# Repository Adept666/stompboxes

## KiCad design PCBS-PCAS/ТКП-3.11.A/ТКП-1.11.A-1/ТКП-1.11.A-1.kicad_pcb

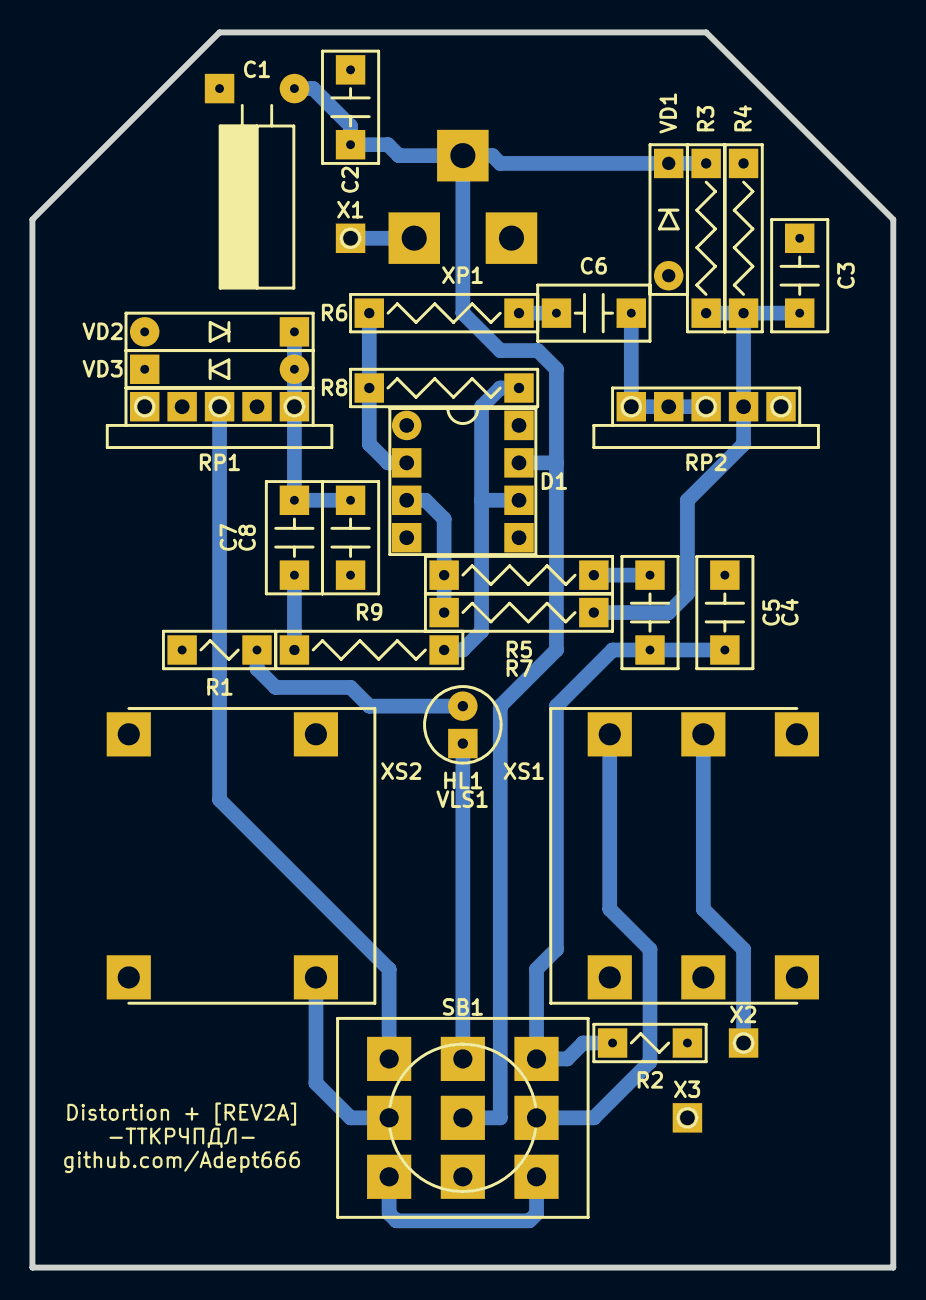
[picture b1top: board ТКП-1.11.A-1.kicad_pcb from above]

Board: 2 copper layers, 58.4 x 83.8 mm, 34 parts (0 on the bottom side), 20 nets.

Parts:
C1: 107; CP-RADIAL-D05.0-P02.0-d0.5-L11-HU
C2: 104; C-DISK-D04.2-T03.0-P05.08-d0.5
C3, C7: 105; C-DISK-D04.2-T03.0-P05.08-d0.5
C4, C8: 102; C-DISK-D04.2-T03.0-P05.08-d0.5
C5: 103; C-DISK-D04.2-T03.0-P05.08-d0.5
C6: 473; C-DISK-D04.2-T03.0-P05.08-d0.5
D1: 741; P-DIP-08
GB1: PP3; B-PP3-HV
HL1: FYL-5013UWC; LED-ROUND-05.0-UNI-SH-SPACER-PNL-5.3
R1: 103; R-MFR-12
R2: 105; R-MFR-12
R3, R4, R7, R8: 105; R-MFR-25
R5, R9: 103; R-MFR-25
R6: 472; R-MFR-25
RP1: A10K; RPB-18-1x17-1.5-PNL-7.4-2.8
RP2: C1M; RPB-18-1x17-1.5-PNL-7.4-2.8
SB1: PBS-24-302SP; SW-PBS-24-302SP-3.0-PNL-13.0
VD1: 400x; P-DO-41
VD2, VD3: 34A; P-DO-7
VE1: B013; B013_A1
VLS1: BR-17.8; VLS-BR
X1: +; CON-PAD-S-1.0-2.0
X2: -; CON-PAD-S-1.0-2.0
X3: COM; CON-PAD-S-1.0-2.0
XP1: 722RA; CON-(L)7X2RA(H)
XS1: NYS215; CON-NYS-215
XS2: NYS2152; CON-NYS-2152

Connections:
/IN-CIR: C4.1, C5.1, R2.2, SB1.NO3
/IN-CON: SB1.COM3, XS1.T
/LED: HL1.A, SB1.NO2
/OUT-CIR: RP1.2, SB1.NO1
/OUT-CON: SB1.COM1, XS2.T
/PP3-NEG: X2.1, XS1.R
/PP3-POS: X1.1, XP1.SN
COM: C1.-, C2.2, C3.2, C4.2, C8.2, D1.4, R1.1, R2.1, R4.1, RP1.1, RP1.NC2, RP2.3, VD1.A, VD2.A, VD3.C, X3.1, XP1.C, XS1.S, XS2.S
unnamed: C5.2, R5.1
unnamed: C6.1, RP2.1, RP2.2, RP2.NC1
unnamed: C6.2, R6.1
unnamed: C7.1, R9.2
unnamed: C7.2, C8.1, RP1.3, VD2.C, VD3.A
unnamed: D1.2, R6.2, R8.1
unnamed: D1.3, R5.2, R7.1
unnamed: D1.6, R8.2, R9.1
unnamed: HL1.C, R1.2
unnamed: SB1.NC1, SB1.NC3
V: C1.+, C2.1, D1.7, R3.2, SB1.COM2, VD1.C, XP1.S
VA: C3.1, R3.1, R4.2, R7.2, RP2.NC2

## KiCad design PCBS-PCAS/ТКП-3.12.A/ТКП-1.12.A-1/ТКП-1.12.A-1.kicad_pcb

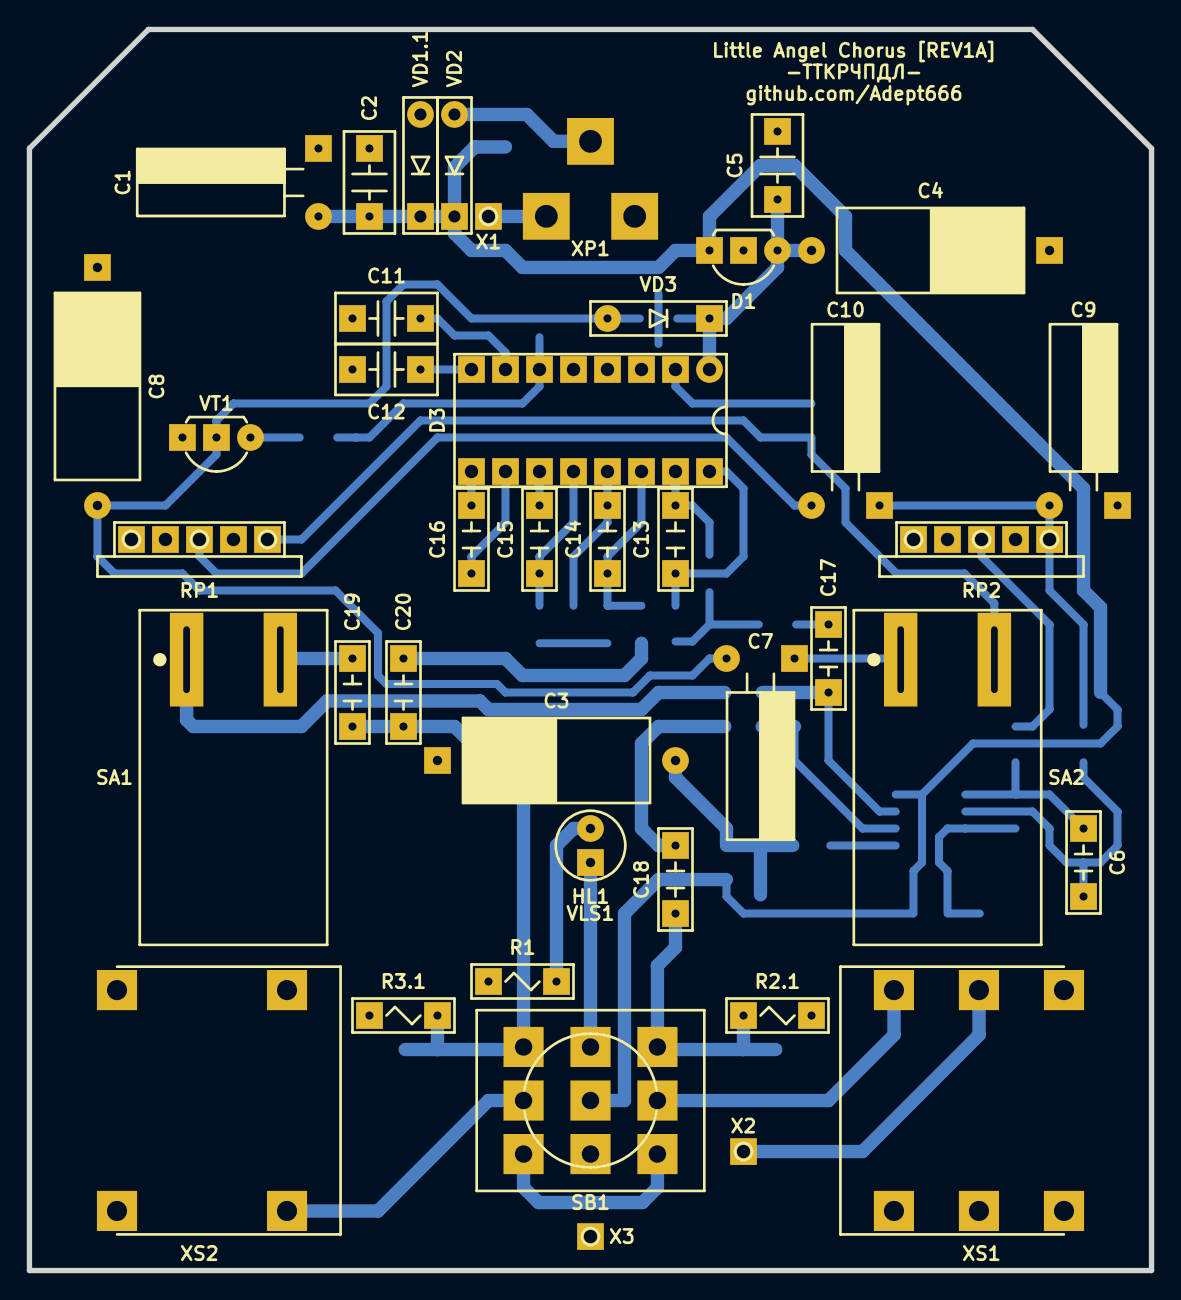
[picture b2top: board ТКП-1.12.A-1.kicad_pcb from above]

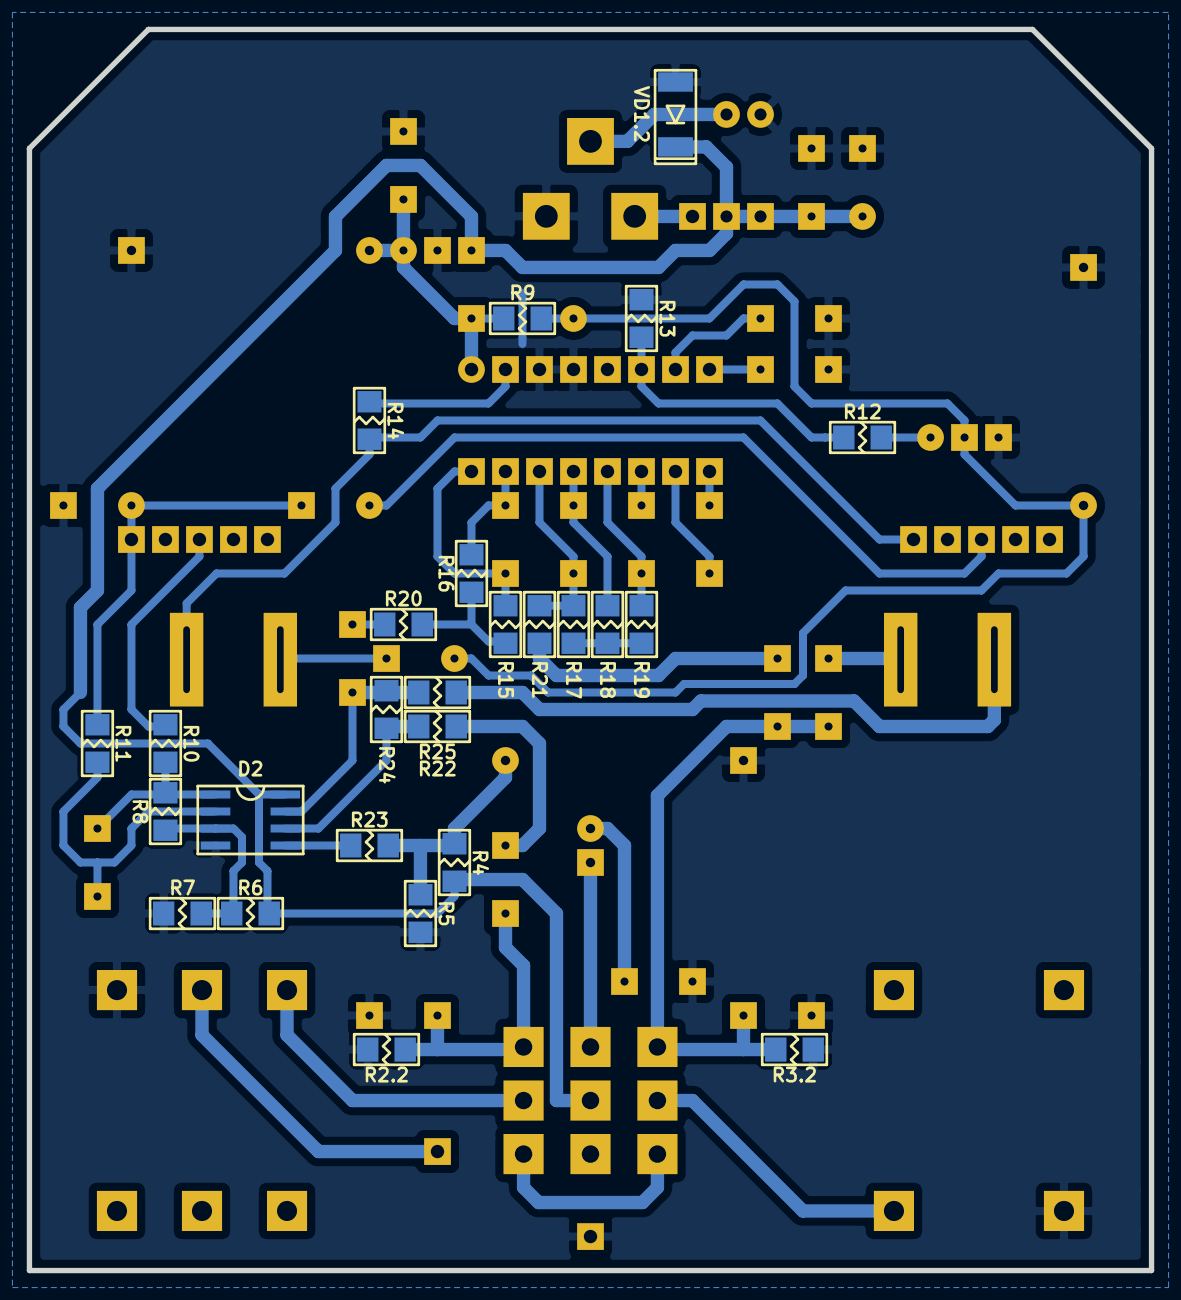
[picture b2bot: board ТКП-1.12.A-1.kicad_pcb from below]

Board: 2 copper layers, 83.8 x 92.7 mm, 70 parts (26 on the bottom side), 46 nets.

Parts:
C1: 107; CP-RADIAL-D05.0-P02.0-d0.5-L11-HU
C2, C5, C11, C12: 104; C-DISK-D04.2-T03.0-P05.08-d0.5
C3, C4, C8: 476; CP-AXIAL-D06-L13-d0.6
C6, C15, C16: 103; C-RECT-L07.3-W02.5-P05.08-d0.5
C7: 106; CP-RADIAL-D05.0-P02.0-d0.5-L11-HD
C9, C10: 106; CP-RADIAL-D05.0-P02.0-d0.5-L11-HU
C13: 332; C-RECT-L07.3-W02.5-P05.08-d0.5
C14: 102; C-RECT-L07.3-W02.5-P05.08-d0.5
C17, C18, C19, C20: 104; C-RECT-L07.3-W02.5-P05.08-d0.5
D1: 78L05; P-TO-92-OUT-GND-IN
D2: 5532; P-SO-08
D3: 2399; P-DIP-16
GB1: PP3; B-PP3-HV
HL1: FYL-5013UWC; LED-ROUND-05.0-UNI-SH-SPACER-PNL-5.3
R1: 103; R-MFR-12
R2.1: 105; R-MFR-12
R2.2, R24: 105; R-SM-1206
R3.1: 104; R-MFR-12
R3.2, R6: 104; R-SM-1206
R4, R5, R15, R16, R17, R18, R19, R20, R21, R25: 103; R-SM-1206
R7: 473; R-SM-1206
R8, R11: 224; R-SM-1206
R9: 683; R-SM-1206
R10: 472; R-SM-1206
R12: 101; R-SM-1206
R13: 222; R-SM-1206
R14: 333; R-SM-1206
R22: 474; R-SM-1206
R23: 334; R-SM-1206
RP1, RP2: B50K; RPB-18-1x12-1.5-PNL-7.4-2.2
SA1, SA2: KN3-1; SW-KN3-1-PNL-13.0
SB1: PBS-24-302SP; SW-PBS-24-302SP-3.0-PNL-13.0
VD1.1: X; P-DO-41
VD1.2: X; P-SOD-87
VD2: 5817; P-DO-41
VD3: 4148; P-DO-35
VE1: G0473; G0473_A1
VLS1: BR-17.8; VLS-BR
VT1: 3904; P-TO-92-C-B-E
X1: +; CON-PAD-S-1.0-2.0
X2: -; CON-PAD-S-1.0-2.0
X3: COM; CON-PAD-S-1.0-2.0
XP1: 722RA; CON-(L)7X2RA(H)
XS1: NYS215; CON-NYS-215
XS2: NYS2152; CON-NYS-2152

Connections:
/IN-CIR: C18.1, R2.1.2, R2.2.2, SB1.NO3
/IN-CON: SB1.COM3, XS1.T
/LED: HL1.A, SB1.NO2
/OUT-CIR: C19.2, C20.2, R3.1.2, R3.2.2, SB1.NO1
/OUT-CON: SB1.COM1, XS2.T
/PP3-NEG: X2.1, XS1.R
/PP3-POS: X1.1, XP1.SN
COM: C1.-, C2.2, C3.-, C4.-, C5.2, C8.-, C9.-, C11.1, C12.1, D1.GND, D2.4, D3.3, D3.4, R1.1, R2.1.1, R2.2.1, R3.1.1, R3.2.1, R5.1, R7.1, R13.1, VD1.1.A, VD1.2.A, VT1.E, X3.1, XP1.C, XS1.S, XS2.S
unnamed: C6.1, D2.1, R8.2, R10.1
unnamed: C6.2, D2.2, R11.1
unnamed: C7.+, C8.+, R9.1, VD3.A, VT1.B
unnamed: C7.-, SA2.COM
unnamed: C10.+, RP1.2
unnamed: C9.+, C10.-, R11.2, RP2.3
unnamed: C11.2, D3.7
unnamed: C12.2, D3.8
unnamed: C13.1, D3.16, R15.1
unnamed: C13.2, D3.15, R16.1
unnamed: C14.1, D3.14, R17.1, R21.1
unnamed: C14.2, D3.13, R18.1
unnamed: C15.1, D3.12, R19.1
unnamed: C15.2, D3.11
unnamed: C16.1, D3.10
unnamed: C16.2, D3.9
unnamed: C17.1, R20.2
unnamed: C17.2, D2.7, R24.2, R25.1
unnamed: C18.2, R22.1
unnamed: C19.1, SA1.NO
unnamed: C20.1, R21.2
unnamed: D2.5, R23.2
unnamed: D2.6, R22.2, R24.1
unnamed: D3.2, R14.2
unnamed: D3.6, R12.2, R13.2
unnamed: HL1.C, R1.2
unnamed: R10.2, RP2.2
unnamed: R12.1, VT1.C
unnamed: R14.1, RP1.3, SA2.NO
unnamed: R15.2, R16.2, R20.1
unnamed: R17.2, R18.2, R19.2
unnamed: R25.2, SA1.COM
unnamed: SB1.NC1, SB1.NC3
unnamed: VD2.A, XP1.S
V: C1.+, C2.1, D1.IN, D2.8, R4.2, R6.2, SB1.COM2, VD1.1.C, VD1.2.C, VD2.C
VA: C4.+, C5.1, D1.OUT, D3.1, R9.2, VD3.C
VB: C3.+, R4.1, R5.2, R23.1
VC: D2.3, R6.1, R7.2, R8.1

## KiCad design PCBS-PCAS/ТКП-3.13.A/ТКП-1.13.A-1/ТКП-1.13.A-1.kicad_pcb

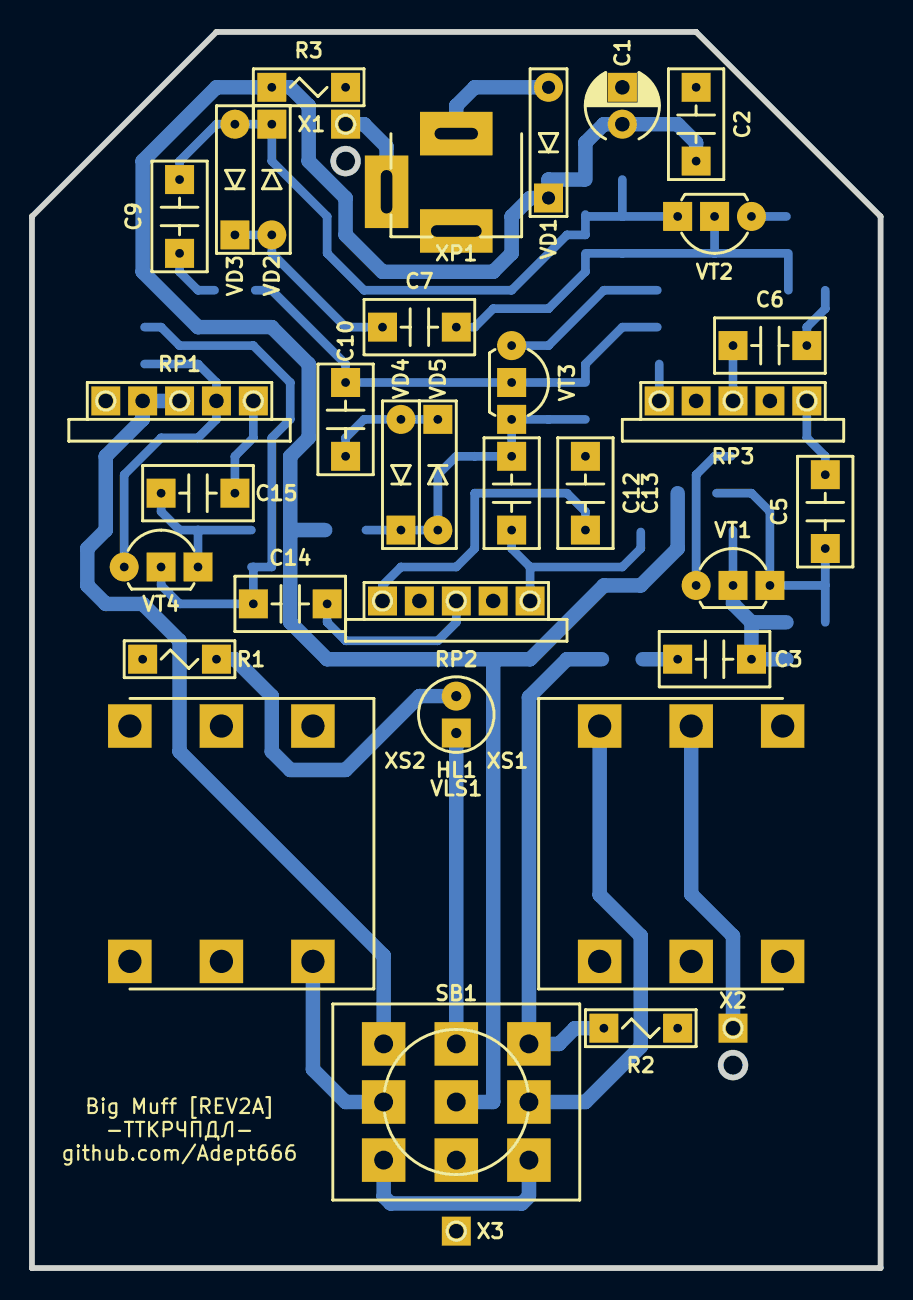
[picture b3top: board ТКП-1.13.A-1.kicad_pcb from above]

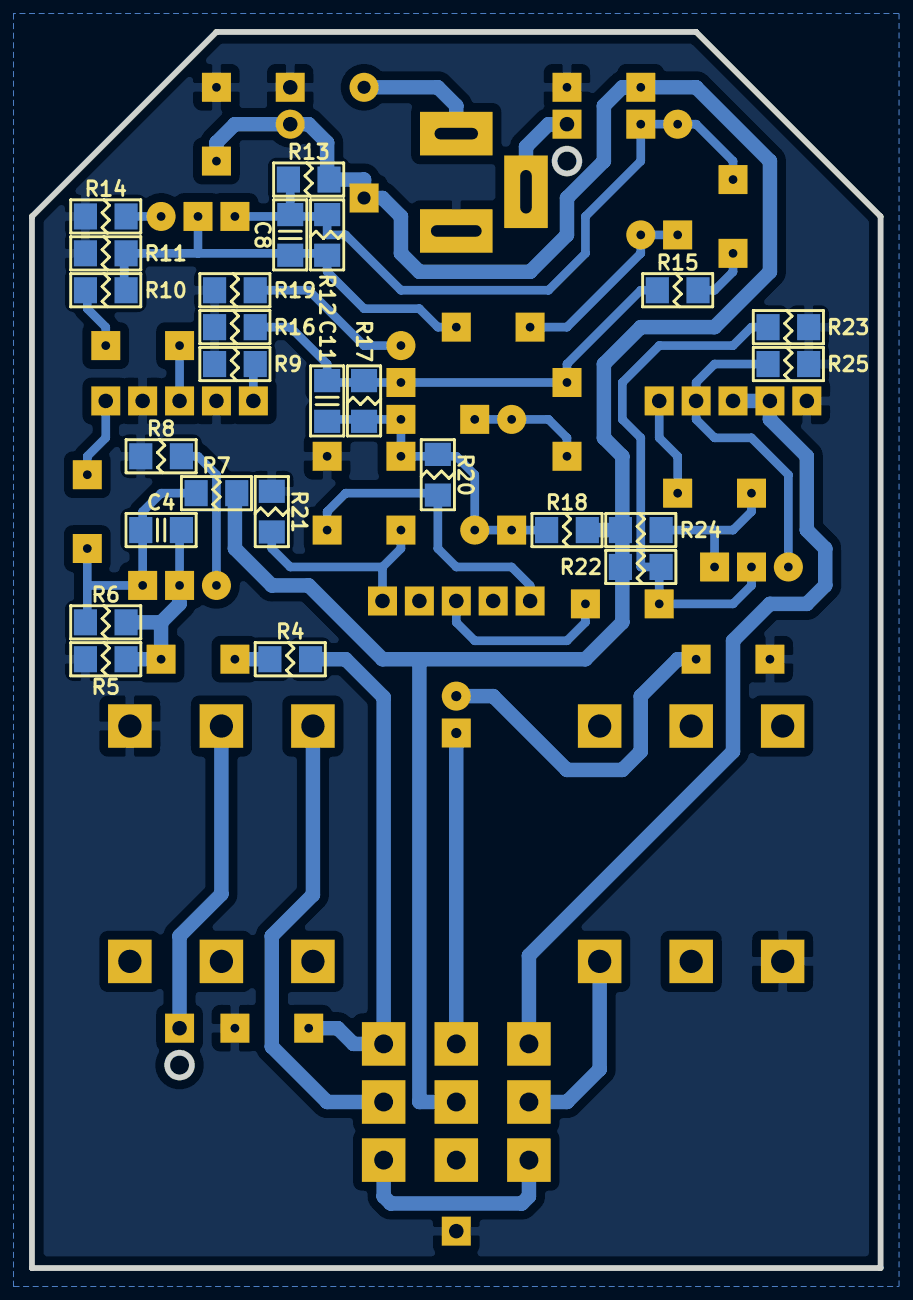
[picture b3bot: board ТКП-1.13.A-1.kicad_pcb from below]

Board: 2 copper layers, 58.4 x 85.1 mm, 63 parts (25 on the bottom side), 36 nets.

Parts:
C1: 106; CP-RADIAL-D05.0-P02.0-CLS
C2: 104; C-DISK-D04.2-T03.0-P05.08-d0.5
C3, C5, C6, C7, C9, C10, C14, C15: 105; C-DISK-D04.2-T03.0-P05.08-d0.5
C4, C8, C11: 471; C-SM-1206
C12: 392; C-DISK-D04.2-T03.0-P05.08-d0.5
C13: 103; C-DISK-D04.2-T03.0-P05.08-d0.5
GB1: PP3; B-PP3-HV
HL1: FYL-5013UWC; LED-ROUND-05.0-UNI-SH-SPACER-PNL-5.3
R1: 103; R-MFR-12
R2: 105; R-MFR-12
R3: X; R-MFR-12
R4: 393; R-SM-1206
R5, R11, R16, R23: 104; R-SM-1206
R6: 514; R-SM-1206
R7, R10, R13, R15, R18, R24: 103; R-SM-1206
R8: 101; R-SM-1206
R9: 182; R-SM-1206
R12, R17, R22: 474; R-SM-1206
R14, R19: 391; R-SM-1206
R20, R21: 223; R-SM-1206
R25: 202; R-SM-1206
RP1, RP3: A100K; RPB-18-1x17-1.5-PNL-7.4-2.8
RP2: B100K; RPB-18-1x17-1.5-PNL-7.4-2.8
SB1: PBS-24-302SP; SW-PBS-24-302SP-3.0-PNL-13.0
VD1: 5817; P-DO-41
VD2, VD3, VD4, VD5: 6263; P-DO-35
VE1: B013; B013_B1
VLS1: BR-17.8; VLS-BR
VT1, VT2, VT3, VT4: 5088; P-TO-92-E-B-C
X1: +; CON-PAD-S-1.0-2.0
X2: -; CON-PAD-S-1.0-2.0
X3: COM; CON-PAD-S-1.0-2.0
XP1: DC-005S; CON-DC-005S
XS1, XS2: PJ-644C; CON-PJ-644C

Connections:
/IN-CIR: R2.2, R4.1, SB1.NO3
/IN-CON: SB1.COM3, XS1.T
/LED: HL1.A, SB1.NO2
/OUT-CIR: RP1.2, RP1.NC1, SB1.NO1
/OUT-CON: SB1.COM1, XS2.T
/PP3-NEG: X2.1, XS1.R
/PP3-POS: X1.1, XP1.SN
COM: C1.-, C2.2, C13.2, R1.1, R2.1, R3.1, R5.1, R8.1, R9.1, R11.1, R14.1, R16.1, R19.1, R21.2, R23.1, R25.1, RP1.1, RP3.NC1, RP3.NC2, X3.1, XP1.C, XS1.S, XS2.S
unnamed: C3.1, R4.2
unnamed: C3.2, C4.1, R5.2, R6.1, VT1.B
unnamed: C4.2, C5.1, R6.2, R7.1, VT1.C
unnamed: C5.2, RP3.3
unnamed: C6.1, RP3.2
unnamed: C6.2, R10.1
unnamed: C7.1, C8.1, R10.2, R11.2, R12.1, VT2.B
unnamed: C7.2, VD2.A, VD3.C
unnamed: C8.2, C9.1, R12.2, R13.1, VD2.C, VD3.A, VT2.C
unnamed: C9.2, R15.1
unnamed: C10.1, C11.1, R15.2, R16.2, R17.1, VT3.B
unnamed: C10.2, VD4.A, VD5.C
unnamed: C11.2, C12.1, R17.2, R18.1, R20.1, VD4.C, VD5.A, VT3.C
unnamed: C12.2, R21.1, RP2.3
unnamed: C13.1, R20.2, RP2.1
unnamed: C14.1, RP2.2
unnamed: C14.2, R22.1, R23.2, VT4.B
unnamed: C15.1, R24.1, VT4.C
unnamed: C15.2, RP1.3
unnamed: HL1.C, R1.2
unnamed: R8.2, VT1.E
unnamed: R9.2, RP3.1
unnamed: R14.2, VT2.E
unnamed: R19.2, VT3.E
unnamed: R25.2, VT4.E
unnamed: SB1.NC1, SB1.NC3
unnamed: VD1.A, XP1.S
V: C1.+, C2.1, R3.2, R7.2, R13.2, R18.2, R22.2, R24.2, SB1.COM2, VD1.C

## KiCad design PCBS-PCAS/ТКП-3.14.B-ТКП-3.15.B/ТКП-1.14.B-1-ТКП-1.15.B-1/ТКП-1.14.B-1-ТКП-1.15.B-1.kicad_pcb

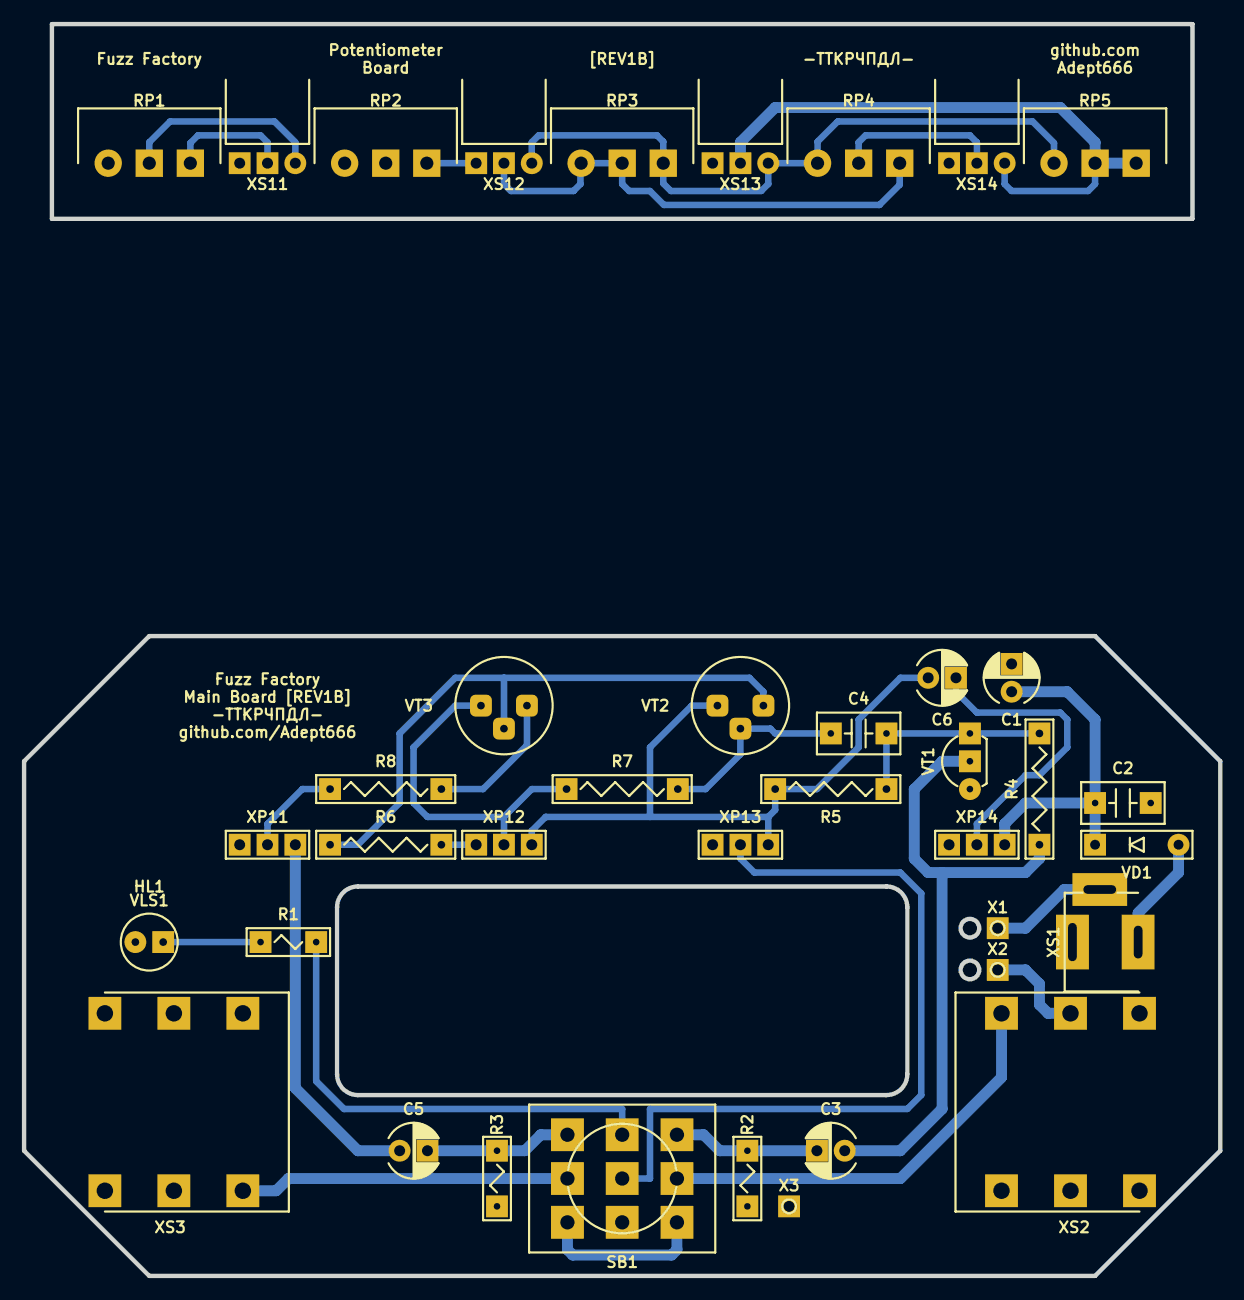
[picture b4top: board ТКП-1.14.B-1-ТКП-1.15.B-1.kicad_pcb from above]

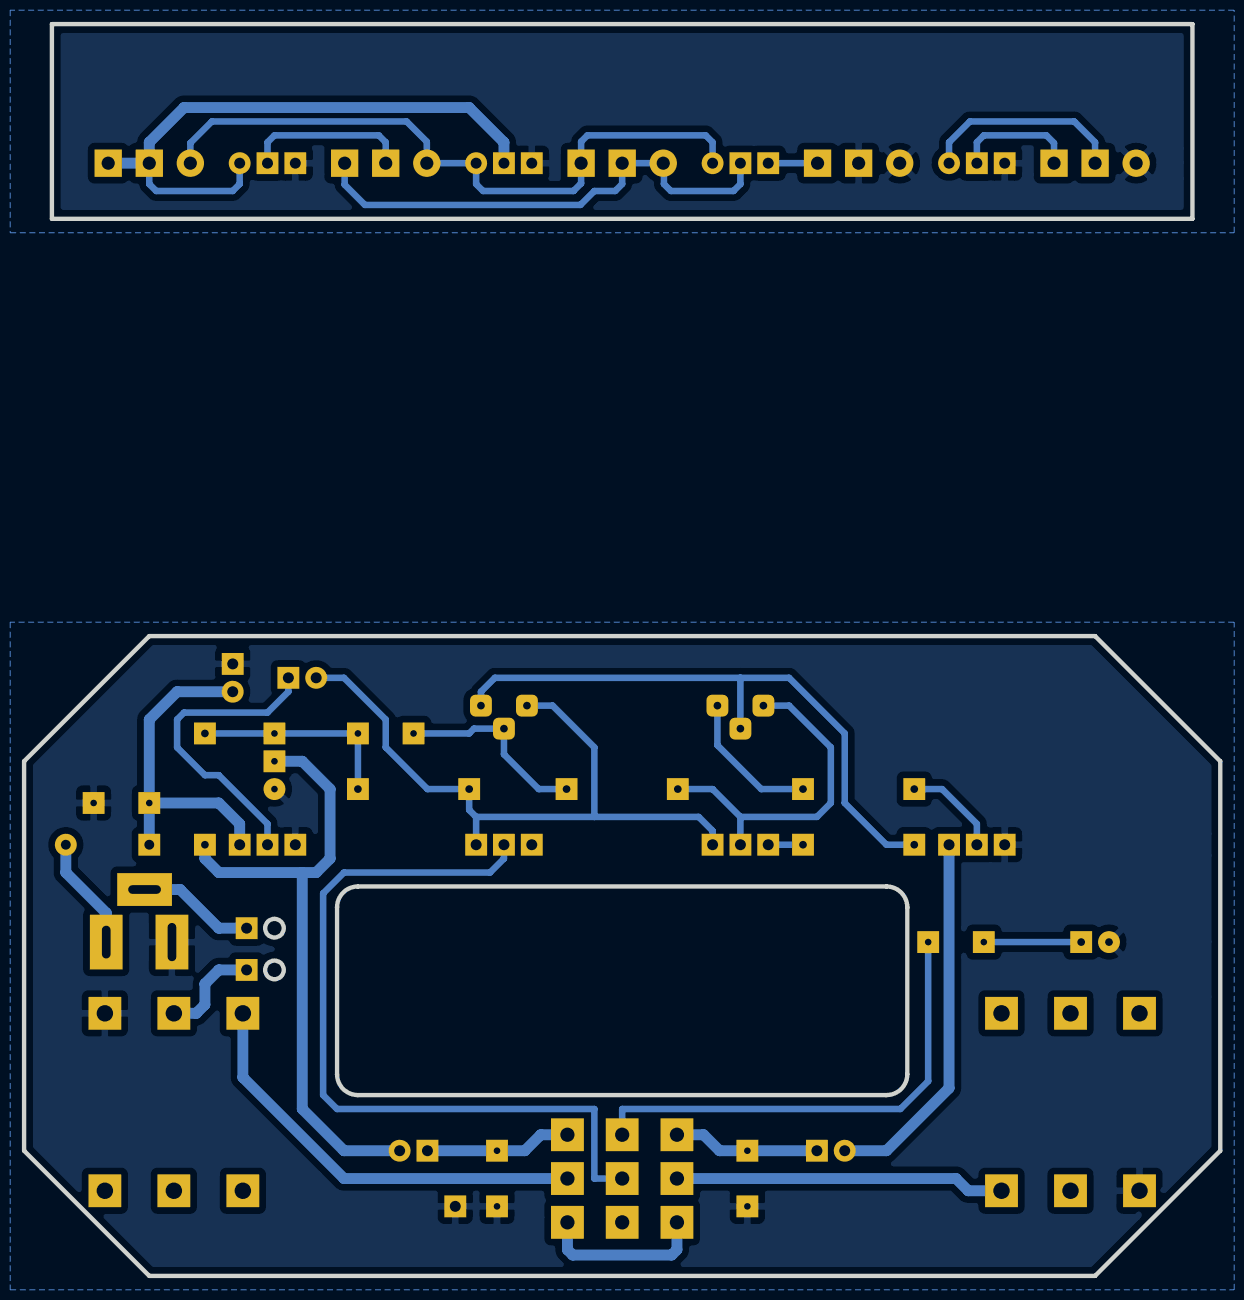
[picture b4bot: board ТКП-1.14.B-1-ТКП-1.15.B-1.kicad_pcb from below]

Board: 2 copper layers, 109.2 x 58.4 mm, 48 parts (6 on the bottom side), 31 nets.

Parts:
C1: 107; CP-RADIAL-D05.0-P02.0-CLS
C2, C4: 104; C-DISK-D04.2-T03.0-P05.08-d0.5
C3, C5, C6: 106; CP-RADIAL-D05.0-P02.0-CLS
GB1: PP3; B-PP3-HV
HL1: FYL-5013UWC; LED-ROUND-05.0-UNI-SH-SPACER-PNL-5.3
R1: 103; R-MFR-12
R2: 105; R-MFR-12
R3: 224; R-MFR-12
R4: 224; R-MFR-25
R5: 103; R-MFR-25
R6: 471; R-MFR-25
R7: 473; R-MFR-25
R8: 512; R-MFR-25
RP1, RP5: B5K; RP-RK1233N1-L15-KC
RP2, RP3, RP4: B10K; RP-RK1233N1-L15-KC
SB1: PBS-24-302SP; SW-PBS-24-302SP-3.0-PNL-13.0
VD1: 5817; P-DO-41
VE1: B013; B013_C1
VJ1.1, VJ1.2, VJ2.1, VJ2.2: BOTTOM; VJ
VLS1: BR-17.8; VLS-BR
VT1: 3904; P-TO-92-E-B-C
VT2, VT3: МП40; P-КТЮ-3-6
VTC1, VTC2: BOTTOM; VTC
X1: +; CON-PAD-S-1.0-2.0
X2: -; CON-PAD-S-1.0-2.0
X3: COM; CON-PAD-S-1.0-2.0
XP11, XP12, XP13, XP14: PLS-03; CON-PLS-03
XS1: DC-005; CON-DC-005
XS2, XS3: PJ-644C; CON-PJ-644C
XS11, XS12, XS13, XS14: PBS-03R; CON-PBS-03R

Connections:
/IN-CIR: C3.-, R2.2, SB1.NO3
/IN-CON: SB1.COM3, XS2.T
/LED: R1.2, SB1.NO2, VJ2.2.1
/MB1: R8.1, XP11.2
/MB2: C5.+, XP11.1
/MB3: R6.1, XP12.3
/MB4: R7.2, VT3.E, XP12.2
/MB5: C6.+, R5.2, VT2.E, XP12.1, XP13.1
/MB7: C6.-, XP14.2
/OUT-CIR: C5.-, R3.2, SB1.NO1
/OUT-CON: SB1.COM1, XS3.T
/PB1: RP1.3, XS11.2
/PB2: RP1.2, XS11.1
/PB3: RP2.3, XS12.3
/PB4: RP3.1, RP3.2, RP4.3, XS12.2
/PB5: RP3.3, RP4.1, RP5.1, XS12.1, XS13.1
/PB7: RP4.2, XS14.2
/PBCOM: RP1.1, RP2.1, RP2.2, XS11.3, XS13.3, XS14.3
/PBV: RP5.2, RP5.3, XS13.2, XS14.1
/PP3-NEG: X2.1, XS2.R
/PP3-POS: X1.1, XS1.SN
COM: C1.-, C2.2, HL1.C, R2.1, R3.1, VT1.E, X3.1, XP11.3, XP14.3, XS1.C, XS2.S, XS3.S
unnamed: C3.+, R4.1, VT1.B
unnamed: C4.1, R4.2, R5.1, VT1.C
unnamed: C4.2, R7.1, VT2.B
unnamed: HL1.A, R1.1
unnamed: R6.2, VT2.C, VT3.B
unnamed: R8.2, VT3.C
unnamed: SB1.NC1, SB1.NC3
unnamed: VD1.A, XS1.S
V: C1.+, C2.1, SB1.COM2, VD1.C, VJ1.1.1, VJ1.2.1, VJ2.1.1, VTC1.1, VTC2.1, XP13.2, XP14.1

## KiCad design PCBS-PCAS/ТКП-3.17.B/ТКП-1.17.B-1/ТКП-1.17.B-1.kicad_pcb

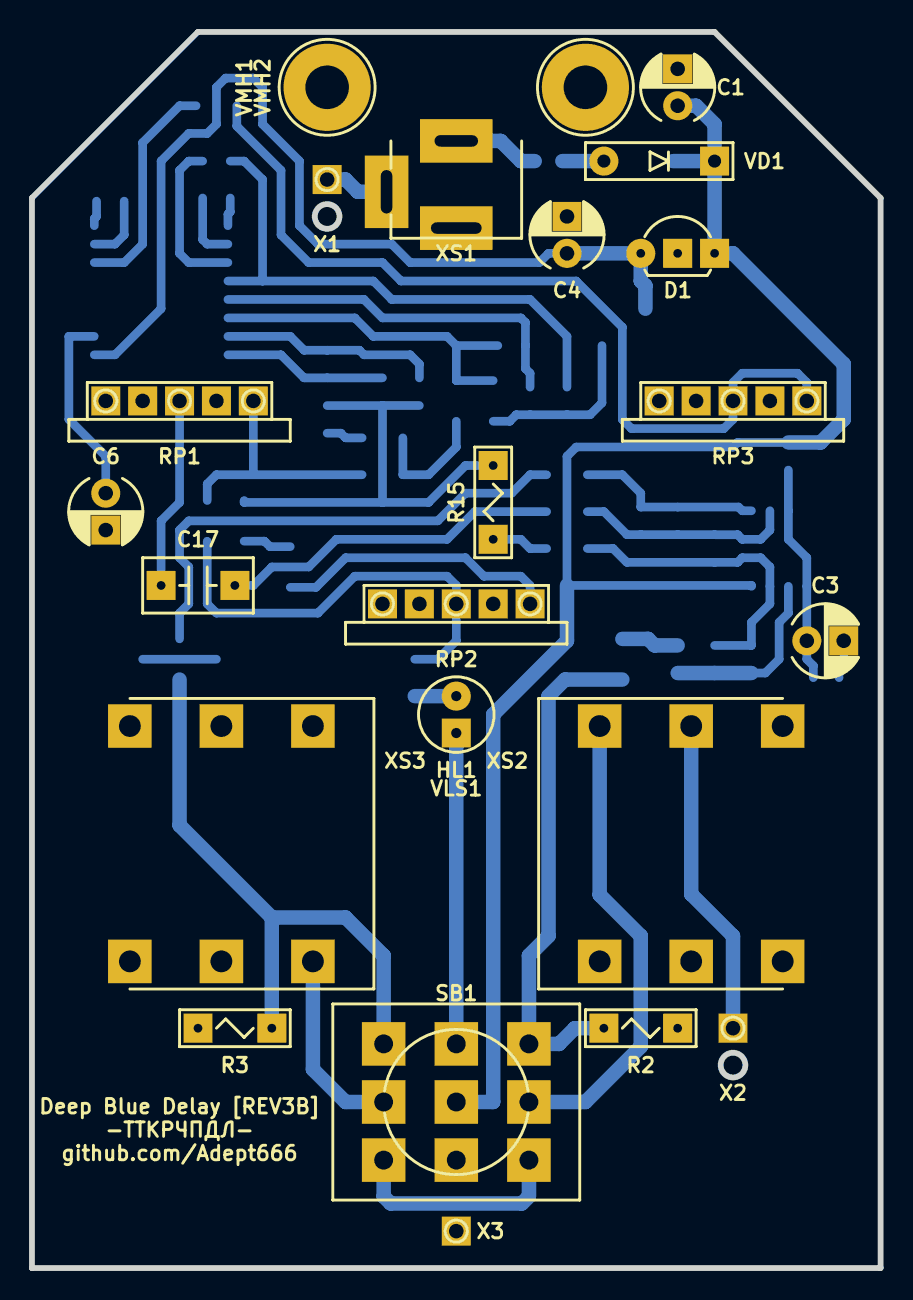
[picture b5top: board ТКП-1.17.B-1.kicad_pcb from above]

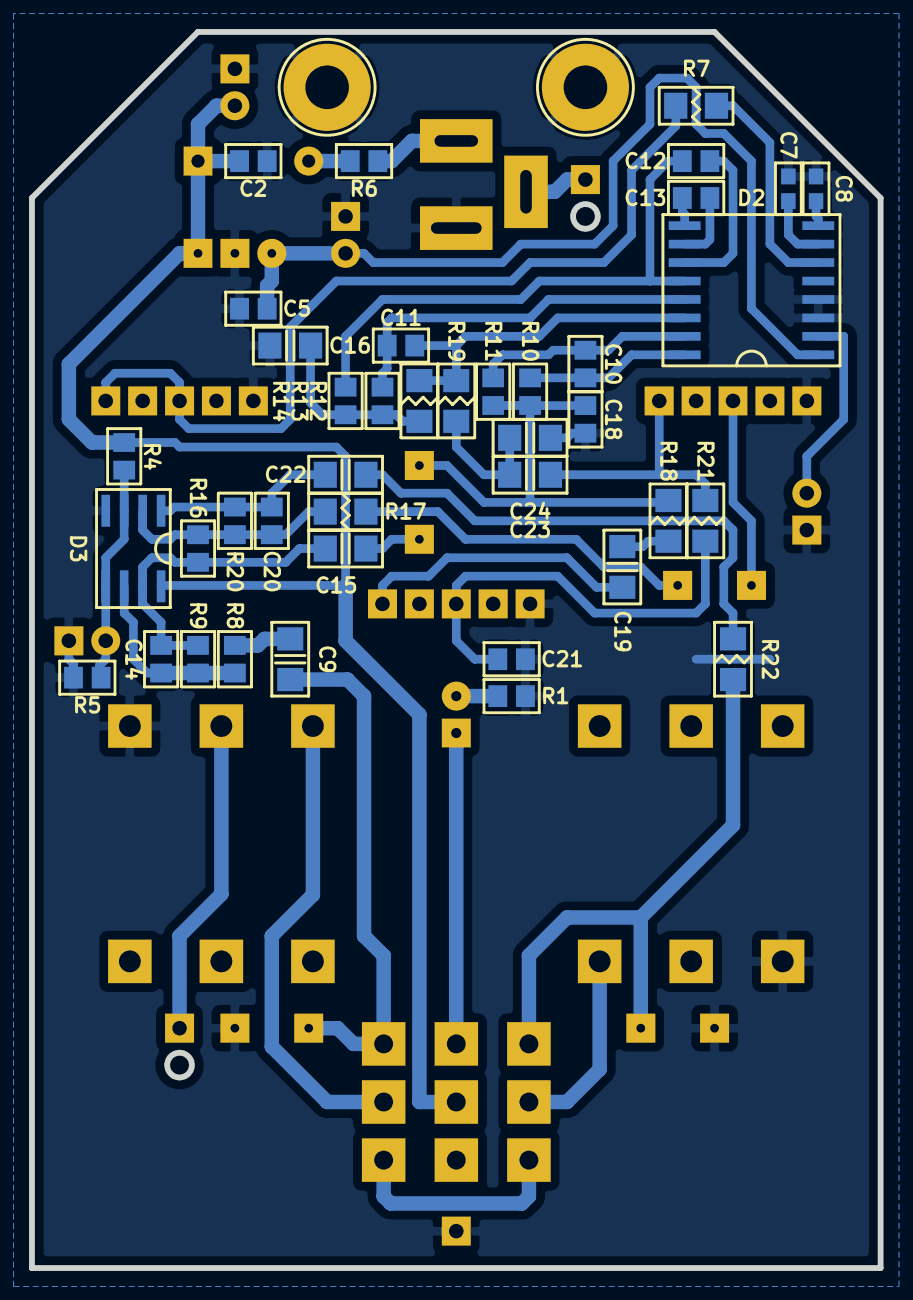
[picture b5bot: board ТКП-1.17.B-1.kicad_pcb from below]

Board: 2 copper layers, 58.4 x 85.1 mm, 66 parts (40 on the bottom side), 44 nets.

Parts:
C1: 107; CP-RADIAL-D05.0-P02.0-CLS
C2, C5, C12, C13: 104; C-SM-0805
C3, C4, C6: 476; CP-RADIAL-D05.0-P02.0-CLS
C7, C8: 104; C-SM-0603
C9, C19: 223; C-SM-1206
C10, C11: 222; C-SM-0805
C14: 470; C-SM-0805
C15, C22, C23: 105; C-SM-1206
C16: 153; C-SM-1206
C17: 105; C-DISK-D04.2-T03.0-P05.08-d0.5
C18: 472; C-SM-0805
C20: 101; C-SM-0805
C21: 473; C-SM-0805
C24: 103; C-SM-1206
D1: 78L05; P-TO-92-OUT-GND-IN
D2: 8970; P-SO-16W
D3: 5532; P-SO-08
GB1: PP3; B-PP3-HV
HL1: FYL-5013UWC; LED-ROUND-05.0-UNI-SH-SPACER-PNL-5.3
R1, R4, R5, R10, R11, R13, R14: 103; R-SM-0805
R2: 105; R-MFR-12
R3: 104; R-MFR-12
R6: 0; R-SM-0805
R7: 272; R-SM-1206
R8: 184; R-SM-0805
R9: 364; R-SM-0805
R12, R17: 203; R-SM-1206
R15: 103; R-MFR-12
R16: 223; R-SM-0805
R18: 512; R-SM-1206
R19, R22: 102; R-SM-1206
R20: 123; R-SM-0805
R21: 202; R-SM-1206
RP1, RP2, RP3: B50K; RPB-18-1x17-1.5-PNL-7.4-2.8
SB1: PBS-24-302SP; SW-PBS-24-302SP-3.0-PNL-13.0
VD1: 5817; P-DO-41
VE1: B013; B013_E1
VLS1: BR-12.7; VLS-BR
VMH1, VMH2: DI5M3x18; VMH-STA-DA5-PNL-3.0
X1: +; CON-PAD-S-1.0-2.0
X2: -; CON-PAD-S-1.0-2.0
X3: COM; CON-PAD-S-1.0-2.0
XS1: DC-005; CON-DC-005
XS2, XS3: PJ-644C; CON-PJ-644C

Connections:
/IN-CIR: C9.1, R2.2, SB1.NO3
/IN-CON: SB1.COM3, XS2.T
/LED: HL1.A, SB1.NO2
/OUT-CIR: R3.2, R22.2, SB1.NO1
/OUT-CON: SB1.COM1, XS3.T
/PP3-NEG: X2.1, XS2.R
/PP3-POS: X1.1, XS1.SN
COM: C1.-, C2.2, C3.-, C4.-, C5.2, C6.-, C7.1, C8.1, C16.2, C18.2, C21.2, C24.2, D1.GND, D2.3, D2.4, D3.4, R1.1, R2.1, R3.1, R5.1, RP1.1, RP2.1, RP3.1, VMH1.0, VMH2.0, X3.1, XS1.C, XS2.S, XS3.S
unnamed: C6.+, D2.2
unnamed: C7.2, D2.7
unnamed: C8.2, D2.8
unnamed: C9.2, R8.1
unnamed: C10.1, D2.16, R10.1
unnamed: C10.2, D2.15, R11.1
unnamed: C11.1, D2.14, R12.1, R19.1
unnamed: C11.2, D2.13, R13.1
unnamed: C12.1, D2.12, R14.1
unnamed: C12.2, D2.11
unnamed: C13.1, D2.10
unnamed: C13.2, D2.9
unnamed: C14.1, D3.6, R8.2, R9.1
unnamed: C14.2, C15.1, D3.7, R9.2, R16.1
unnamed: C15.2, R15.2
unnamed: C16.1, R12.2, R13.2, R14.2
unnamed: C17.1, R17.1
unnamed: C17.2, RP1.2
unnamed: C18.1, R10.2, R11.2, R15.1, R18.2
unnamed: C19.1, R18.1
unnamed: C19.2, RP2.3
unnamed: C20.1, D3.2, R16.2, R17.2, R20.1
unnamed: C20.2, C22.1, D3.1, R20.2
unnamed: C21.1, R21.1, RP2.2
unnamed: C22.2, R22.1
unnamed: C23.1, R21.2, RP1.3
unnamed: C23.2, C24.1, R19.2
unnamed: D2.6, R7.2
unnamed: HL1.C, R1.2
unnamed: R6.1, XS1.S
unnamed: R6.2, VD1.A
unnamed: R7.1, RP3.2, RP3.3
unnamed: SB1.NC1, SB1.NC3
V: C1.+, C2.1, D1.IN, D3.8, R4.2, SB1.COM2, VD1.C
VA: C4.+, C5.1, D1.OUT, D2.1
VB: C3.+, D3.3, D3.5, R4.1, R5.2

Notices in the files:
PCBS-PCAS/ТКП-3.11.A/ТКП-1.11.A-1/ТКП-1.11.A-1.kicad_pcb:
This project is licensed under GNU General Public License v3.0 or later
